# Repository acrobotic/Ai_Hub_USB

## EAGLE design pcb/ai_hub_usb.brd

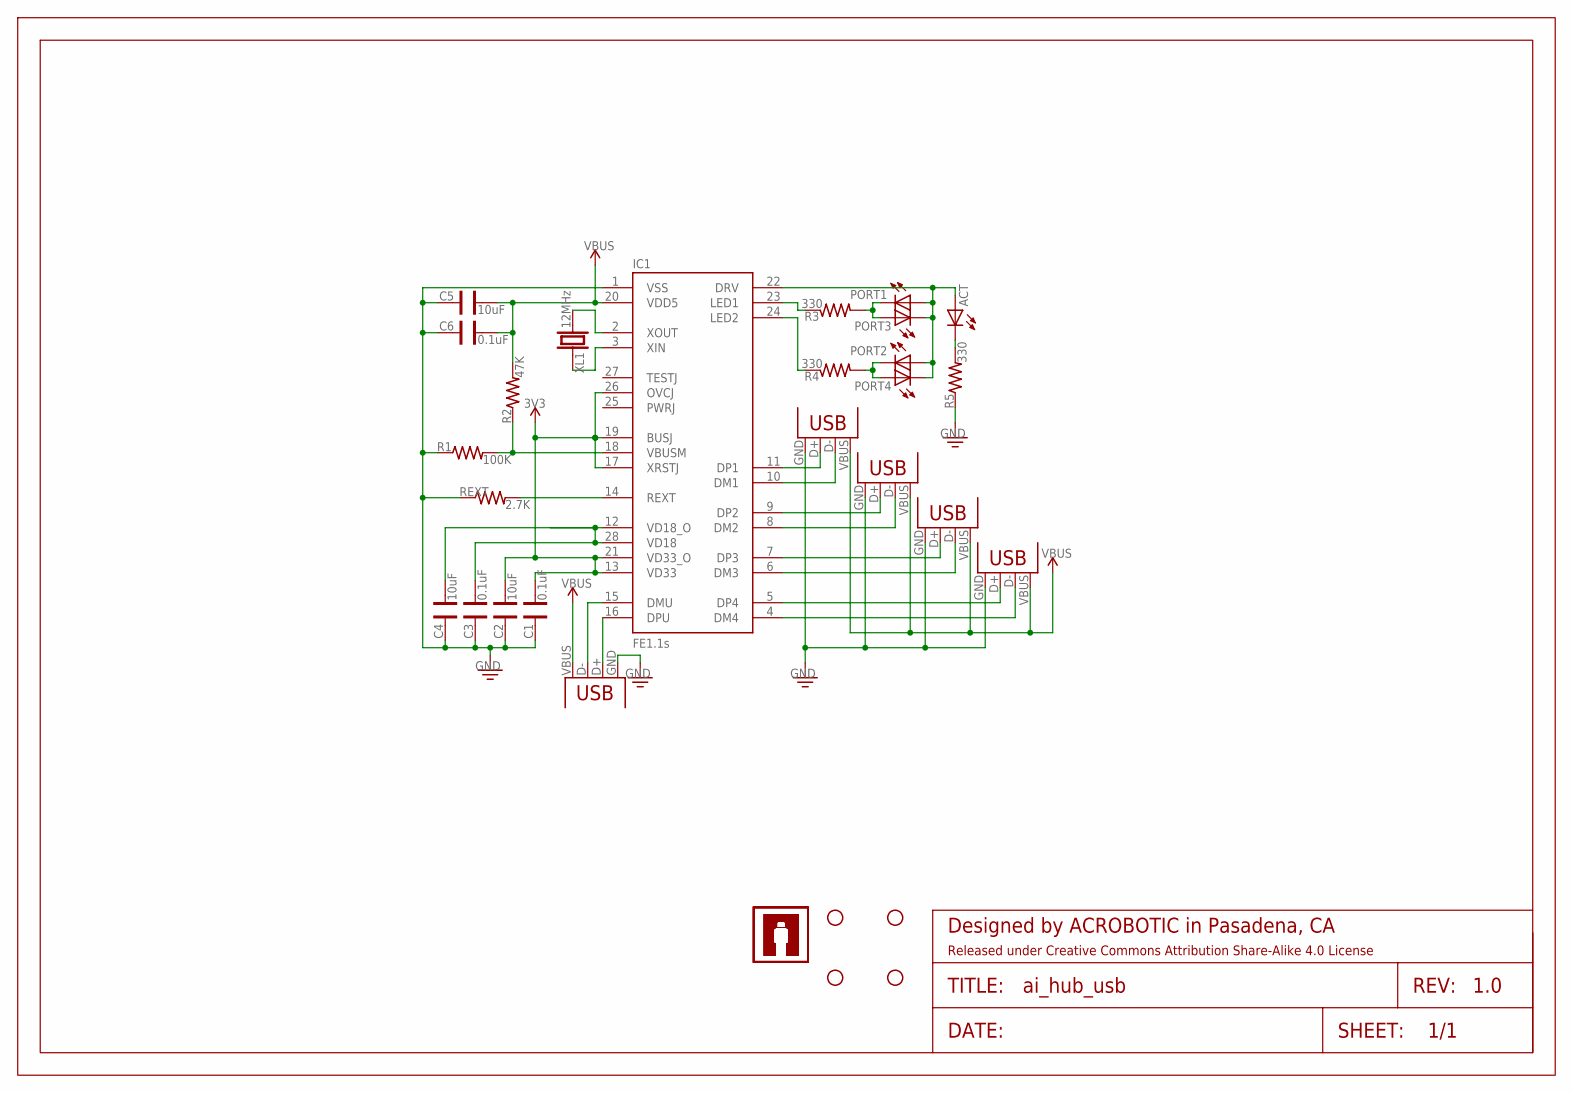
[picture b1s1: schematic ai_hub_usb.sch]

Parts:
ACT: LED0603; LED-0603
C1, C3, C6: 0.1uF; CAP-0603
C2, C4, C5: 10uF; CAP-0603
FRAME1: FRAME-LETTER; CREATIVE-COMMONS
IC1: FE1.1S; FE1.1S_SSOP-28
PORT1, PORT2, PORT3, PORT4: LED0603; LED-0603
R1: 100K; RES-0603
R2: 47K; RES-0603
R3, R4, R5: 330; RES-0603
REXT: 2.7K; RES-0603
STANDOFF1, STANDOFF2, STANDOFF3, STANDOFF4: STAND-OFF4; STAND-OFF-4
U$5, U$6: AI-LOGOXS; AI-LOGO-XS
USB1: USBMICROB-PTH; USB-MICROB-TH
USB2, USB3, USB4, USB5: USBA-PTH; USB-A-F-PTH
XL1: 12MHz; HC49UP

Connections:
3V3: C1.1, C2.1, IC1.13 (VD33), IC1.17 (XRSTJ), IC1.19 (BUSJ), IC1.21 (VD33_O), IC1.26 (OVCJ)
GND: C1.2, C2.2, C3.2, C4.2, C5.2, C6.2, IC1.1 (VSS), R1.1, R5.1, REXT.1, USB1.GND, USB2.GND, USB3.GND, USB4.GND, USB5.GND
unnamed: IC1.14 (REXT), REXT.2
unnamed: IC1.15 (DMU), USB1.D-
unnamed: IC1.16 (DPU), USB1.D+
unnamed: PORT2.C, PORT4.A, R4.2
unnamed: IC1.2 (XOUT), XL1.2
unnamed: C3.1, C4.1, IC1.12 (VD18_O), IC1.28 (VD18)
unnamed: IC1.3 (XIN), XL1.1
unnamed: IC1.11 (DP1), USB5.D+
unnamed: IC1.10 (DM1), USB5.D-
unnamed: IC1.18 (VBUSM), R1.2, R2.1
unnamed: IC1.9 (DP2), USB4.D+
unnamed: IC1.8 (DM2), USB4.D-
unnamed: IC1.7 (DP3), USB3.D+
unnamed: IC1.6 (DM3), USB3.D-
unnamed: IC1.5 (DP4), USB2.D+
unnamed: IC1.4 (DM4), USB2.D-
unnamed: PORT1.C, PORT3.A, R3.2
unnamed: ACT.C, R5.2
unnamed: IC1.23 (LED1), R3.1
unnamed: IC1.24 (LED2), R4.1
unnamed: ACT.A, IC1.22 (DRV), PORT1.A, PORT2.A, PORT3.C, PORT4.C
VBUS: C5.1, C6.1, IC1.20 (VDD5), R2.2, USB1.VBUS, USB2.VBUS, USB3.VBUS, USB4.VBUS, USB5.VBUS

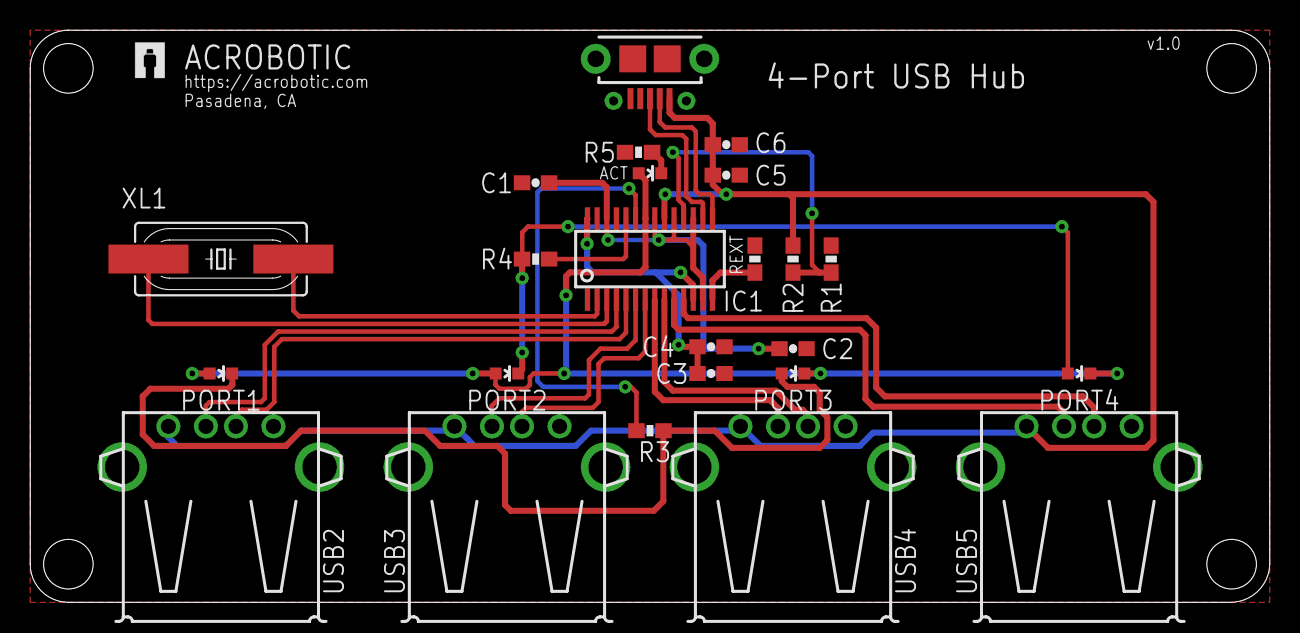
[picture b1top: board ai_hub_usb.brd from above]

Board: 2 copper layers, 82.5 x 38.1 mm, 31 parts (1 on the bottom side), 24 nets.

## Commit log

2015-11-08 updating LED spacing
2015-11-16 minor change

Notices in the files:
parts and their libraries:
Ai_Miscellany: Released under the Creative Commons
Attribution Share-Alike 4.0 License
Ai_Miscellany: https://creativecommons.org/licenses/by-sa/4.0
Ai_Miscellany: Released under Creative Commons Attribution Share-Alike 4.0 License
